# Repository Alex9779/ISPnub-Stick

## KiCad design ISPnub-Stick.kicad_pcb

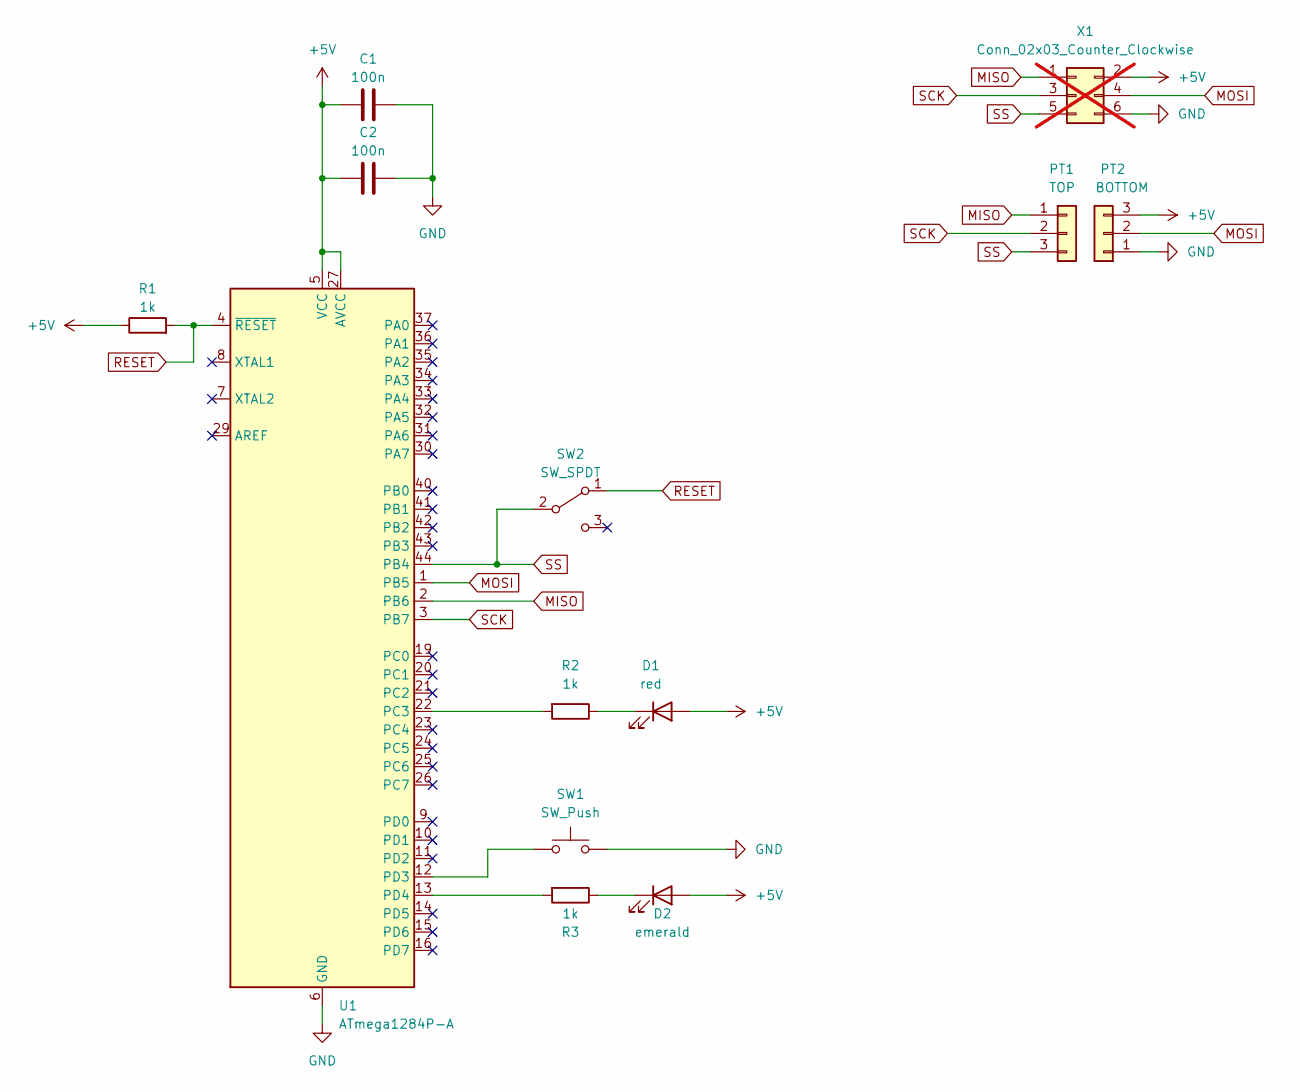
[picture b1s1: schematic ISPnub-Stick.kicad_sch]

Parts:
C1, C2: 100n; C_0603_1608Metric
D1: red; LED_0805_2012Metric; JLCPCB Part # C84256
D2: emerald; LED_0805_2012Metric; JLCPCB Part # C2297
PT1: TOP; Edge_x3
PT2: BOTTOM; Edge_x3
R1, R2, R3: 1k; R_0603_1608Metric
SW1: SW_Push; TS-1187A-B-A-B; JLCPCB Part # C318884
SW2: SW_SPDT; SS-12D02-VG5; JLCPCB Part # C2998802
U1: ATmega1284P-A; TQFP-44_10x10mm_P0.8mm; JLCPCB Rotation Offset -90
X1: Conn_02x03_Counter_Clockwise; IDC-Header_2x03_P2.54mm_Vertical; JLCPCB Rotation Offset -90; not fitted

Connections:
+5V: C1.2, C2.2, D1.2 (A), D2.2 (A), PT2.3, R1.1, U1.5 (VCC), U1.17 (VCC), U1.27 (AVCC), U1.38 (VCC), X1.2
GND: C1.1, C2.1, PT2.1, SW1.2, U1.6 (GND), U1.18 (GND), U1.28 (GND), U1.39 (GND), X1.6
MISO: PT1.1, U1.2 (PB6), X1.1
MOSI: PT2.2, U1.1 (PB5), X1.4
unnamed: D1.1 (K), R2.1
unnamed: D2.1 (K), R3.1
unnamed: R2.2, U1.22 (PC3)
unnamed: SW1.1, U1.12 (PD3)
unnamed: R3.2, U1.13 (PD4)
RESET: R1.2, SW2.1 (A), U1.4 (~RESET)
SCK: PT1.2, U1.3 (PB7), X1.3
SS: PT1.3, SW2.2 (B), U1.44 (PB4), X1.5

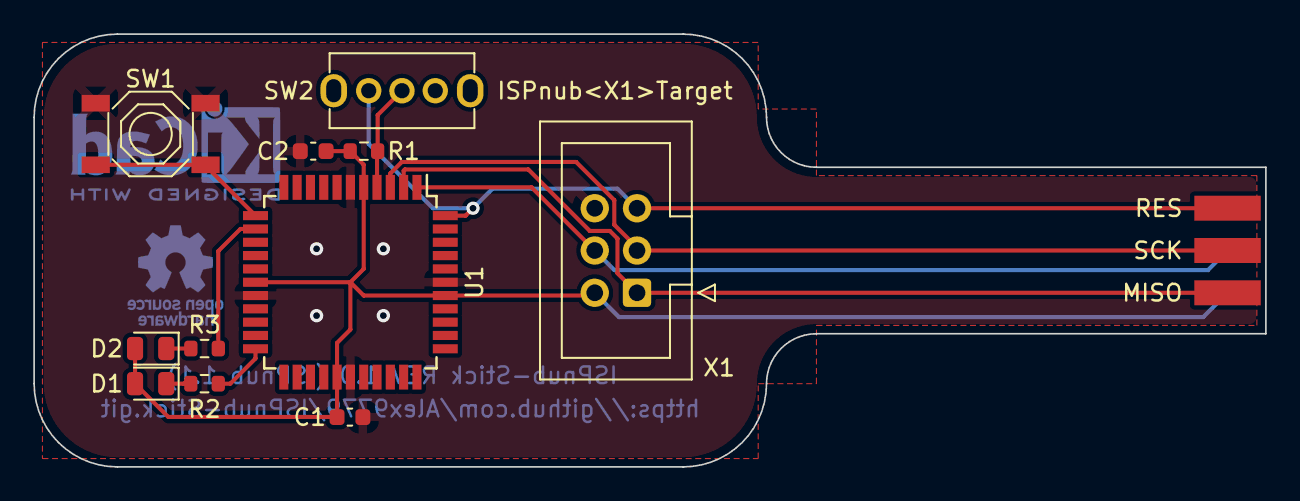
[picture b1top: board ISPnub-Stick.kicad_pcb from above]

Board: 2 copper layers, 74.0 x 26.0 mm, 13 parts (1 on the bottom side), 12 nets.

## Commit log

2023-11-16 rev1.0 changes
